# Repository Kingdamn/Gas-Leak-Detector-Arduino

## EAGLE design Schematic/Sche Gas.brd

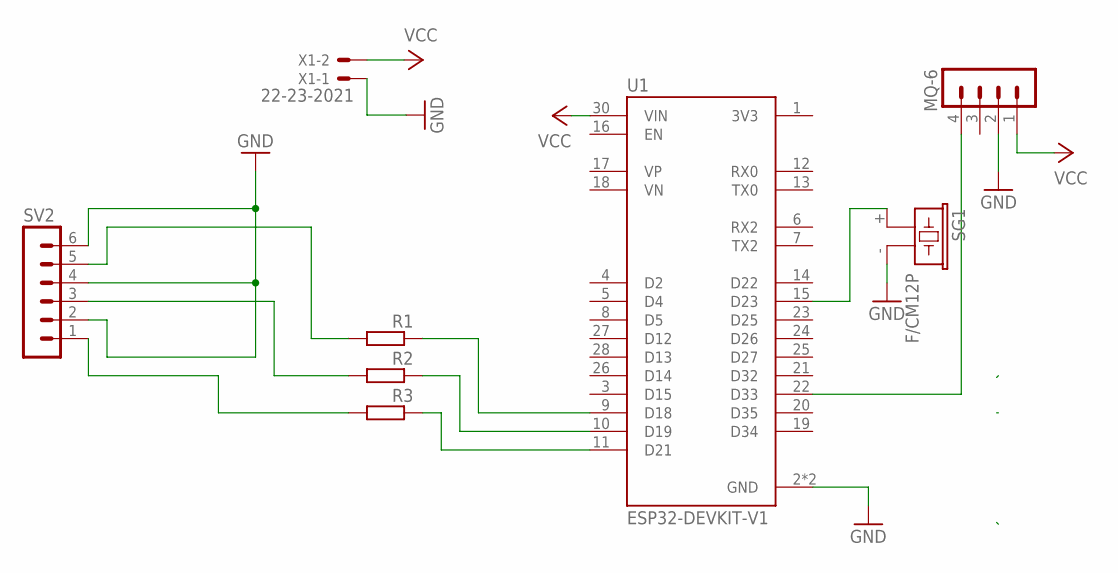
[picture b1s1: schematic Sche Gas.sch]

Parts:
MQ-6: MA04-1
R1, R2, R3: R-EU_0204/7; 0204/7
SG1: F/CM12P
SV2: MA06-1
U1: ESP32-DEVKIT-V1; MODULE_ESP32_DEVKIT_V1
X1: 22-23-2021

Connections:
GND: MQ-6.2, SG1.- (2), SV2.2, SV2.4, SV2.6, U1.2 (GND), U1.29 (GND), X1.1
unnamed: SG1.+ (1), U1.15 (D23)
unnamed: R1.1, U1.9 (D18)
unnamed: MQ-6.4, U1.22 (D33)
unnamed: R3.1, U1.11 (D21)
unnamed: R1.2, SV2.5
unnamed: R2.2, SV2.3
unnamed: R3.2, SV2.1
unnamed: R2.1, U1.10 (D19)
VCC: MQ-6.1, U1.30 (VIN), X1.2

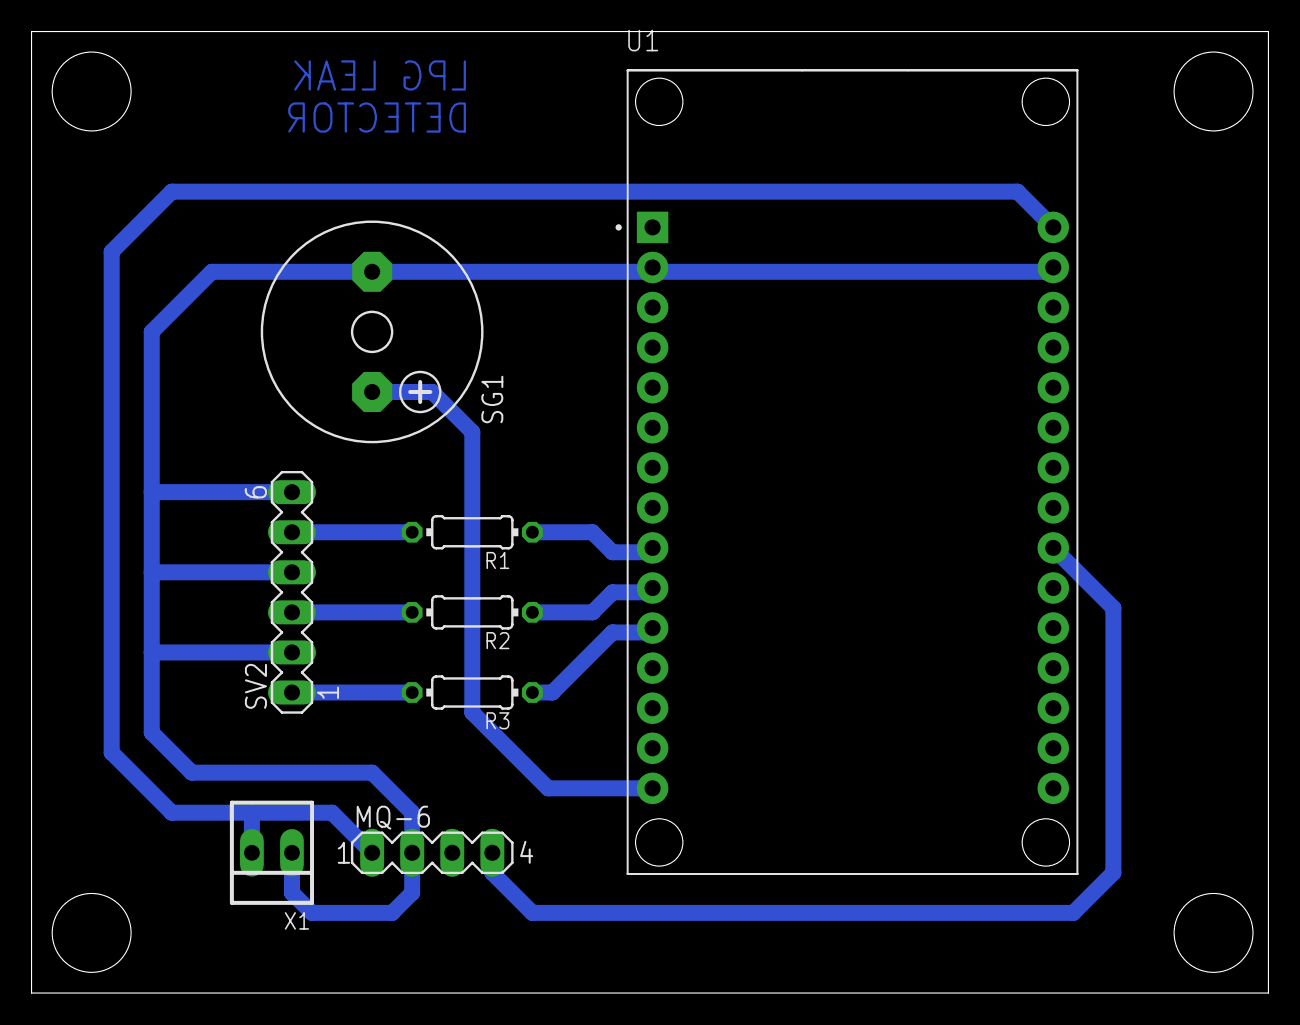
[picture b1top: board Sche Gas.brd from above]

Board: 2 copper layers, 78.4 x 60.9 mm, 8 parts (0 on the bottom side), 10 nets.

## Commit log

2024-06-06 Arduino Gas Leak Detector
